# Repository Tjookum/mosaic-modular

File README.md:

# mosaic-modular
Basic guidelines and design files for the mosaic modular format

For updates and more info visit the electro-music.com topic: http://electro-music.com/forum/viewtopic.php?p=444554#444554

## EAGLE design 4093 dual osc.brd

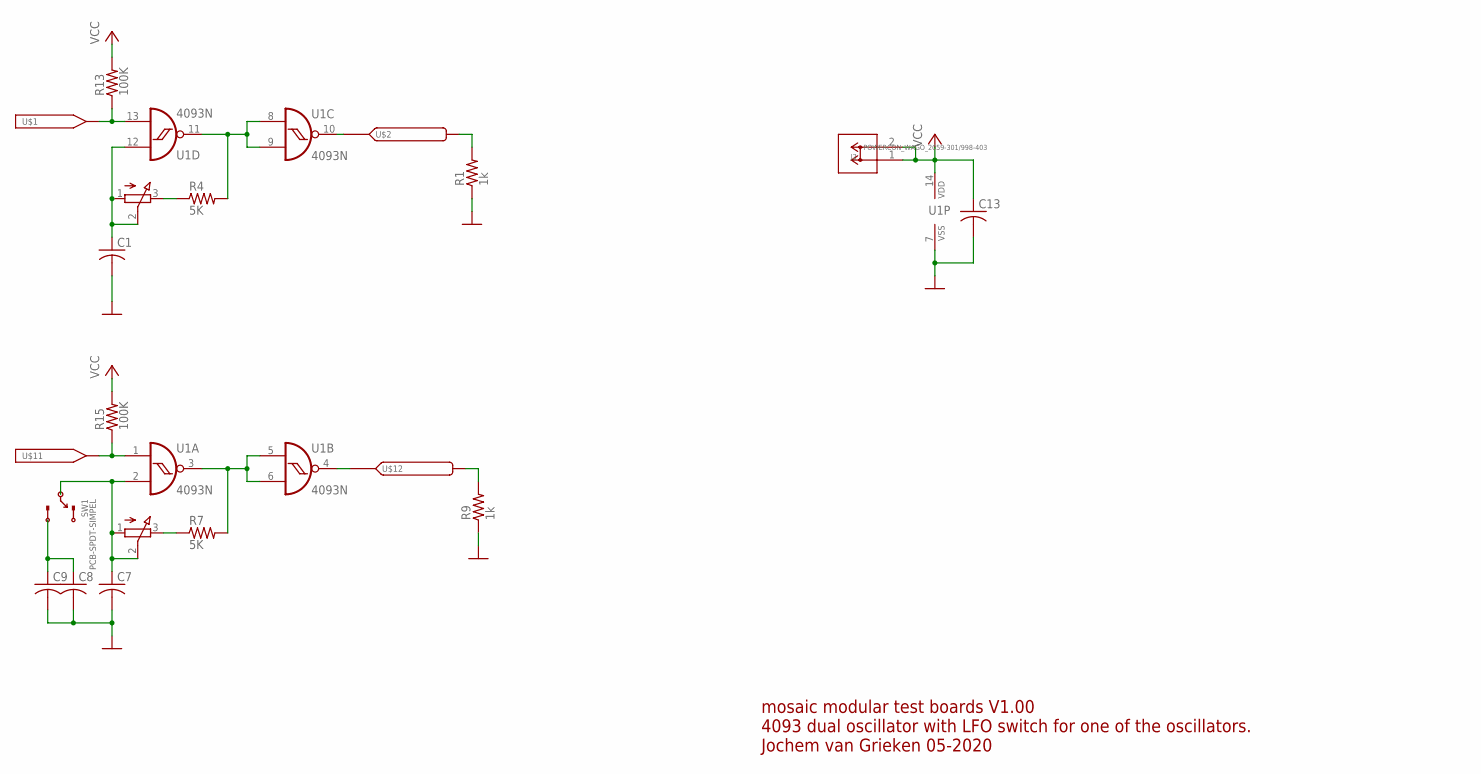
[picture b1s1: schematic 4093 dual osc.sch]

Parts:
1, 3: ALPHA-16MM-UNDERSIDESMD; ALPHA-16MMPOT-UNDERSIDE-SLOT-SMDPADS
C1, C7, C8, C9, C13: C-USC0805; C0805
J2: POWERCON_WAGO_2059-301/998-403; CONN_2059-301/998-403_2
R1, R9: 1k; R0805
R4, R7: 5K; R0805
R13, R15: 100K; R0805
SW1: PCB-SPDT-SIMPEL; SPDT-SLIDE
U1: 4093N; DIL14
U$1, U$11: IN; BANANA_NOLED
U$2, U$12: OUT; BANANA_LED

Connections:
GND: C1.2, C7.2, C8.2, C9.2, C13.2, R1.1, R9.1, U1.7 (VSS)
unnamed: R1.2, U$2.OUTERRING, U$2.OUTERRING2
unnamed: C8.1, C9.1, SW1.3
unnamed: U1.10 (O), U$2.>NAME, U$2.INNERRING, U$2.INNERRING2
unnamed: U1.4 (O), U$12.>NAME, U$12.INNERRING, U$12.INNERRING2
unnamed: 1.3, R4.1
unnamed: 1.1, 1.2, C1.1, U1.12 (I0)
unnamed: R13.1, U1.13 (I1), U$1.P$1
unnamed: R4.2, U1.8 (I0), U1.9 (I1), U1.11 (O)
unnamed: 3.3, R7.1
unnamed: 3.1, 3.2, C7.1, SW1.2, U1.2 (I1)
unnamed: R15.1, U1.1 (I0), U$11.P$1
unnamed: R7.2, U1.3 (O), U1.5 (I0), U1.6 (I1)
unnamed: R9.2, U$12.OUTERRING, U$12.OUTERRING2
VCC: C13.1, J2.1, J2.2, R13.2, R15.2, U1.14 (VDD)

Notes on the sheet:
mosaic modular test boards V1.00 4093 dual oscillator with LFO switch for one of the oscillators. Jochem van Grieken 05-2020

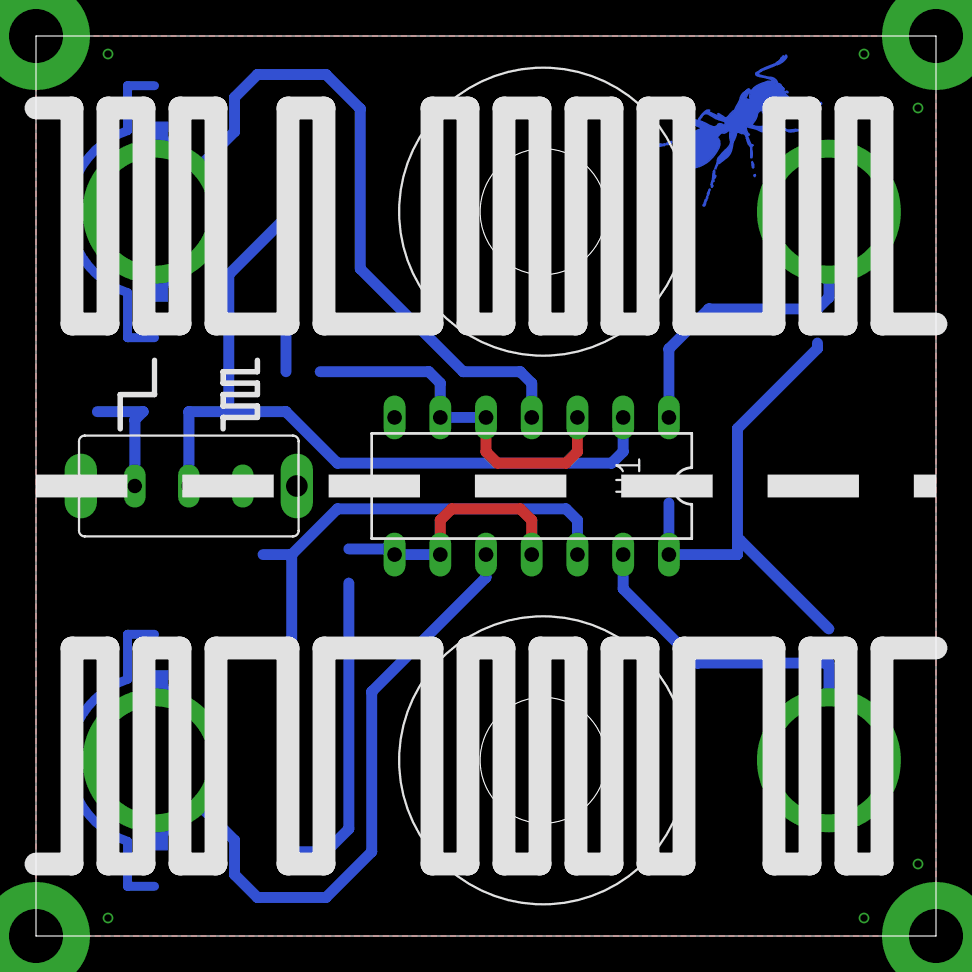
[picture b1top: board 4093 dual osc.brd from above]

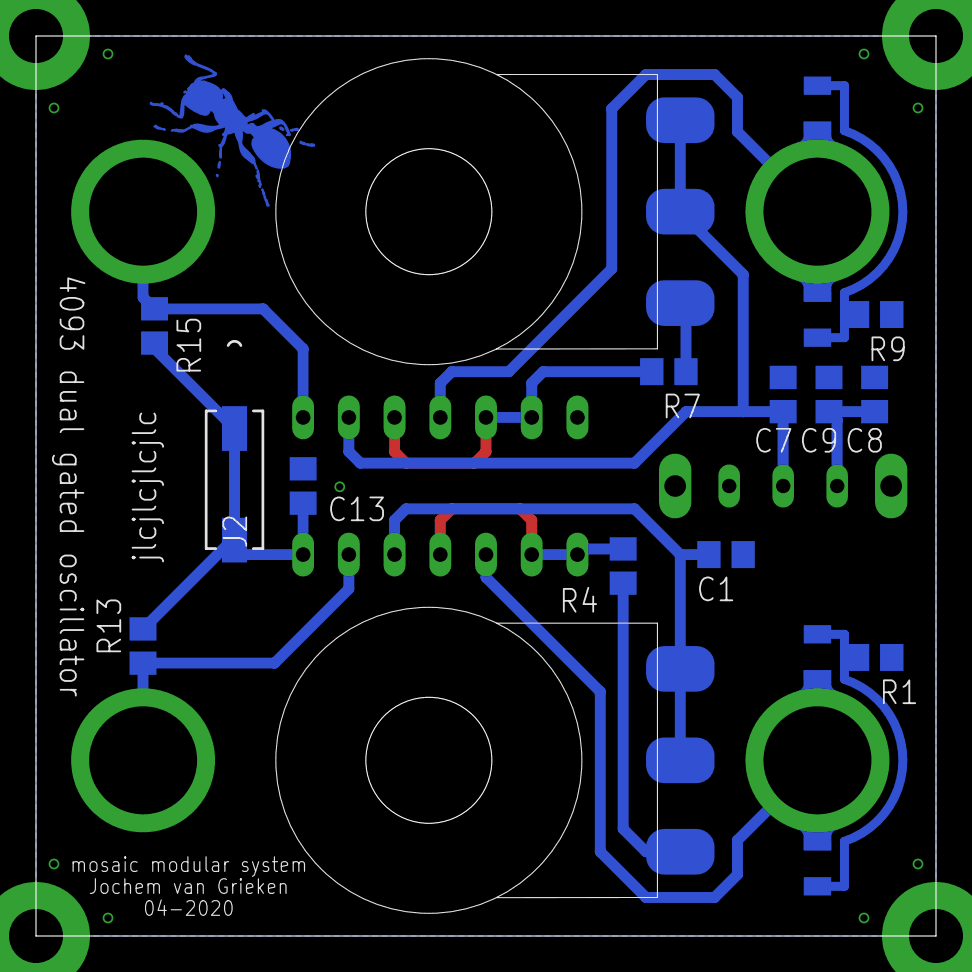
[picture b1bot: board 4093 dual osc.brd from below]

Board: 2 copper layers, 50.0 x 50.0 mm, 21 parts (12 on the bottom side), 15 nets.

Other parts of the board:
U$3: ANT_LOGO_COPPER_BOTTOM

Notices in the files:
parts and their libraries:
COPYRIGHT: Copyright (C) 2018 Accelerated Designs. All rights reserved
